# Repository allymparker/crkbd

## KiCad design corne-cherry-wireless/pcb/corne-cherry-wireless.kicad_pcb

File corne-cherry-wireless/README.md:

# Corne Choc Wireless

## Motivation
- Love the Corne form factor
- Love Nice!Nano
- Want Nice!View with no monkey patching
- Love the Ultralight, but want Choc Hotswap
  - Want the On/Off switch
  - Want the JST connector

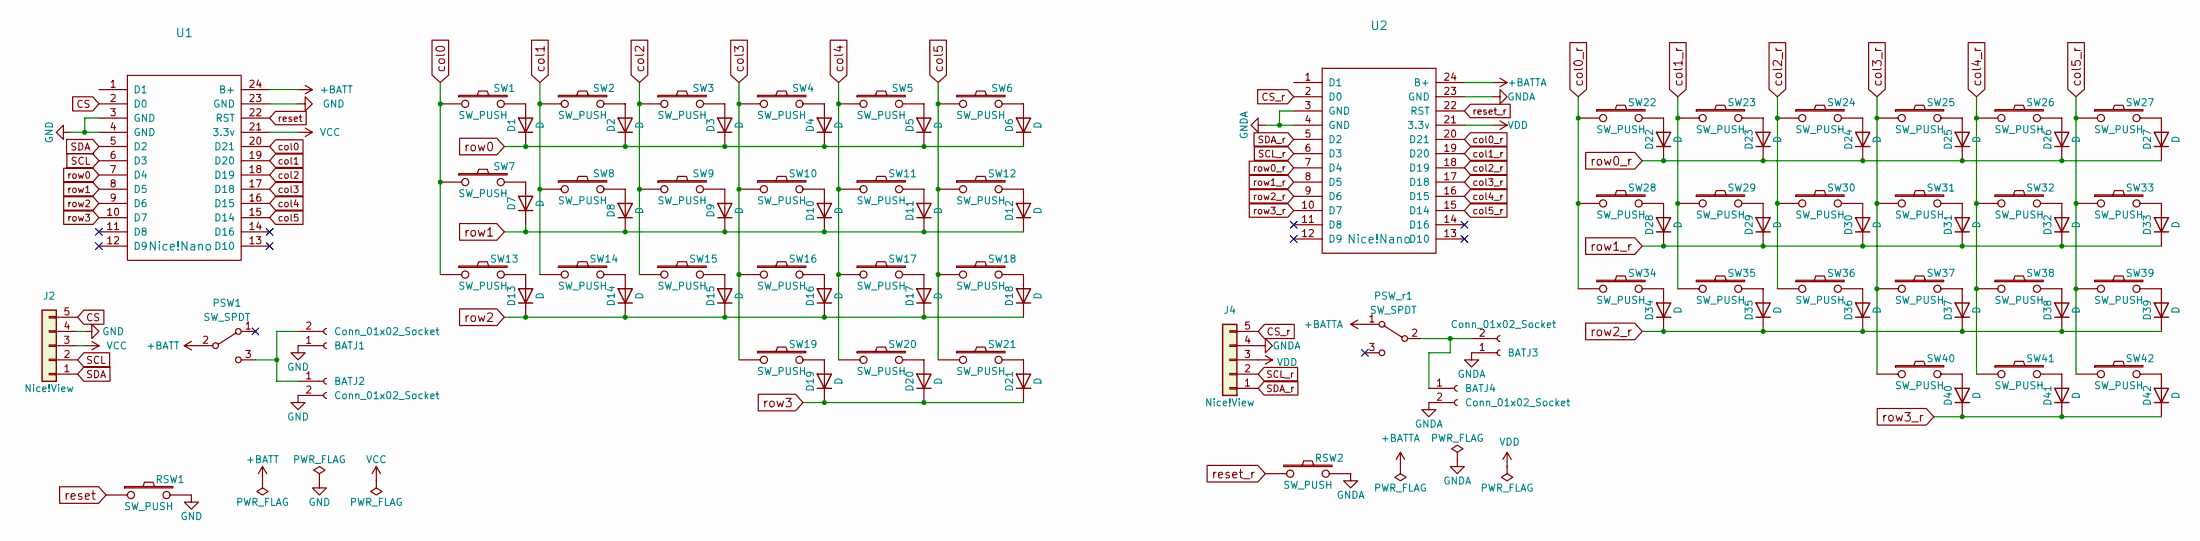
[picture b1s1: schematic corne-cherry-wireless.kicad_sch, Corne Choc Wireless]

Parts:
BATJ1, BATJ3: Conn_01x02_Socket; PinHeader_1x02_P2.54mm_Vertical
BATJ2, BATJ4: Conn_01x02_Socket; JST_PH_S2B-PH-K_1x02_P2.00mm_Horizontal
D1, D2, D3, D4, D5, D6, D7, D8, D9, D10, D11, D12, D13, D14, D15, D16, D17, D18, D19, D20, D21, D22, D23, D24, D25, D26, D27, D28, D29, D30, D31, D32, D33, D34, D35, D36, D37, D38, D39, D40, D41, D42: D; D3_SMD_v2
J2, J4: Nice!View; nice_view_1side
PSW1: SW_SPDT; SW_SPDT_PCM12
PSW_r1: SW_SPDT; SW_SPDT_PCM12
RSW1, RSW2: SW_PUSH; ResetSW_1side
SW1, SW2, SW3, SW4, SW5, SW6, SW7, SW8, SW9, SW10, SW11, SW12, SW13, SW14, SW15, SW16, SW17, SW18, SW19, SW20, SW22, SW23, SW24, SW25, SW26, SW27, SW28, SW29, SW30, SW31, SW32, SW33, SW34, SW35, SW36, SW37, SW38, SW39, SW40, SW41: SW_PUSH; CherryMX_Hotswap
SW21, SW42: SW_PUSH; CherryMX_Hotswap_1.5u
U1, U2: Nice!Nano; ProMicro_v3

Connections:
+BATT: PSW1.2 (B), U1.24 (B+)
+BATTA: PSW_r1.1 (A), U2.24 (B+)
CS: J2.5, U1.2 (D0)
CS_r: J4.5, U2.2 (D0)
GND: BATJ1.1, BATJ2.2, J2.4, RSW1.2, U1.3 (GND), U1.4 (GND), U1.23 (GND)
GNDA: BATJ3.1, BATJ4.2, J4.4, RSW2.2, U2.3 (GND), U2.4 (GND), U2.23 (GND)
unnamed: BATJ1.2, BATJ2.1, PSW1.3 (C)
unnamed: BATJ3.2, BATJ4.1, PSW_r1.2 (B)
unnamed: D1.2 (A), SW1.2
unnamed: D2.2 (A), SW2.2
unnamed: D3.2 (A), SW3.2
unnamed: D4.2 (A), SW4.2
unnamed: D5.2 (A), SW5.2
unnamed: D6.2 (A), SW6.2
unnamed: D7.2 (A), SW7.2
unnamed: D8.2 (A), SW8.2
unnamed: D9.2 (A), SW9.2
unnamed: D10.2 (A), SW10.2
unnamed: D11.2 (A), SW11.2
unnamed: D12.2 (A), SW12.2
unnamed: D13.2 (A), SW13.2
unnamed: D14.2 (A), SW14.2
unnamed: D15.2 (A), SW15.2
unnamed: D16.2 (A), SW16.2
unnamed: D17.2 (A), SW17.2
unnamed: D18.2 (A), SW18.2
unnamed: D19.2 (A), SW19.2
unnamed: D20.2 (A), SW20.2
unnamed: D21.2 (A), SW21.2
unnamed: D22.2 (A), SW22.2
unnamed: D23.2 (A), SW23.2
unnamed: D24.2 (A), SW24.2
unnamed: D25.2 (A), SW25.2
unnamed: D26.2 (A), SW26.2
unnamed: D27.2 (A), SW27.2
unnamed: D28.2 (A), SW28.2
unnamed: D29.2 (A), SW29.2
unnamed: D30.2 (A), SW30.2
unnamed: D31.2 (A), SW31.2
unnamed: D32.2 (A), SW32.2
unnamed: D33.2 (A), SW33.2
unnamed: D34.2 (A), SW34.2
unnamed: D35.2 (A), SW35.2
unnamed: D36.2 (A), SW36.2
unnamed: D37.2 (A), SW37.2
unnamed: D38.2 (A), SW38.2
unnamed: D39.2 (A), SW39.2
unnamed: D40.2 (A), SW40.2
unnamed: D41.2 (A), SW41.2
unnamed: D42.2 (A), SW42.2
SCL: J2.2, U1.6 (D3)
SCL_r: J4.2, U2.6 (D3)
SDA: J2.1, U1.5 (D2)
SDA_r: J4.1, U2.5 (D2)
VCC: J2.3, U1.21 (3.3v)
VDD: J4.3, U2.21 (3.3v)
col0: SW1.1, SW7.1, SW13.1, U1.20 (D21)
col0_r: SW22.1, SW28.1, SW34.1, U2.20 (D21)
col1: SW2.1, SW8.1, SW14.1, U1.19 (D20)
col1_r: SW23.1, SW29.1, SW35.1, U2.19 (D20)
col2: SW3.1, SW9.1, SW15.1, U1.18 (D19)
col2_r: SW24.1, SW30.1, SW36.1, U2.18 (D19)
col3: SW4.1, SW10.1, SW16.1, SW19.1, U1.17 (D18)
col3_r: SW25.1, SW31.1, SW37.1, SW40.1, U2.17 (D18)
col4: SW5.1, SW11.1, SW17.1, SW20.1, U1.16 (D15)
col4_r: SW26.1, SW32.1, SW38.1, SW41.1, U2.16 (D15)
col5: SW6.1, SW12.1, SW18.1, SW21.1, U1.15 (D14)
col5_r: SW27.1, SW33.1, SW39.1, SW42.1, U2.15 (D14)
reset: RSW1.1, U1.22 (RST)
reset_r: RSW2.1, U2.22 (RST)
row0: D1.1 (K), D2.1 (K), D3.1 (K), D4.1 (K), D5.1 (K), D6.1 (K), U1.7 (D4)
row0_r: D22.1 (K), D23.1 (K), D24.1 (K), D25.1 (K), D26.1 (K), D27.1 (K), U2.7 (D4)
row1: D7.1 (K), D8.1 (K), D9.1 (K), D10.1 (K), D11.1 (K), D12.1 (K), U1.8 (D5)
row1_r: D28.1 (K), D29.1 (K), D30.1 (K), D31.1 (K), D32.1 (K), D33.1 (K), U2.8 (D5)
row2: D13.1 (K), D14.1 (K), D15.1 (K), D16.1 (K), D17.1 (K), D18.1 (K), U1.9 (D6)
row2_r: D34.1 (K), D35.1 (K), D36.1 (K), D37.1 (K), D38.1 (K), D39.1 (K), U2.9 (D6)
row3: D19.1 (K), D20.1 (K), D21.1 (K), U1.10 (D7)
row3_r: D40.1 (K), D41.1 (K), D42.1 (K), U2.10 (D7)

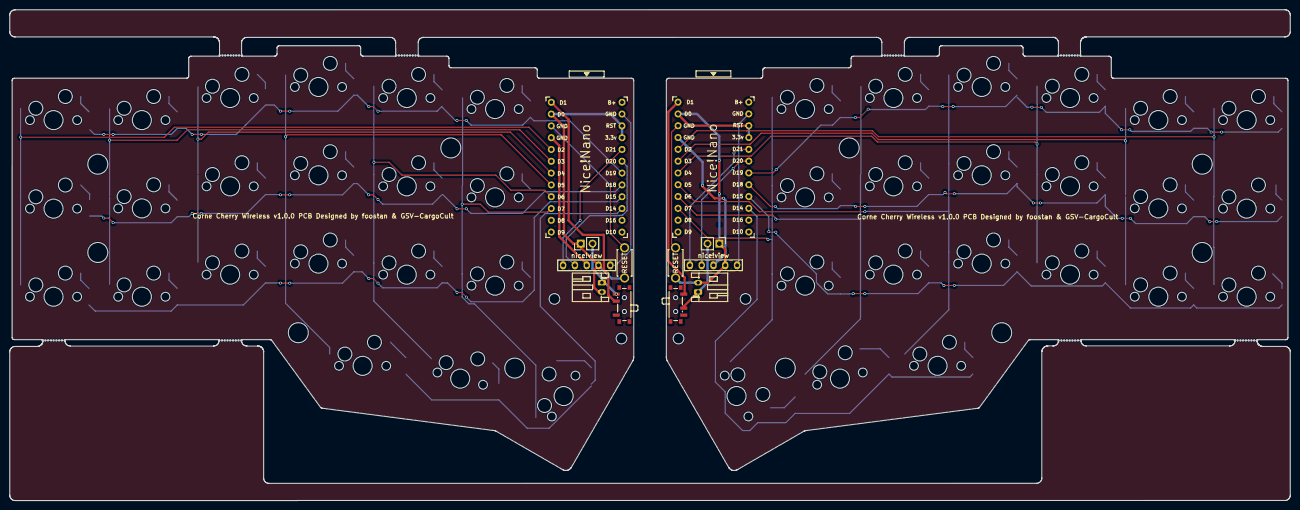
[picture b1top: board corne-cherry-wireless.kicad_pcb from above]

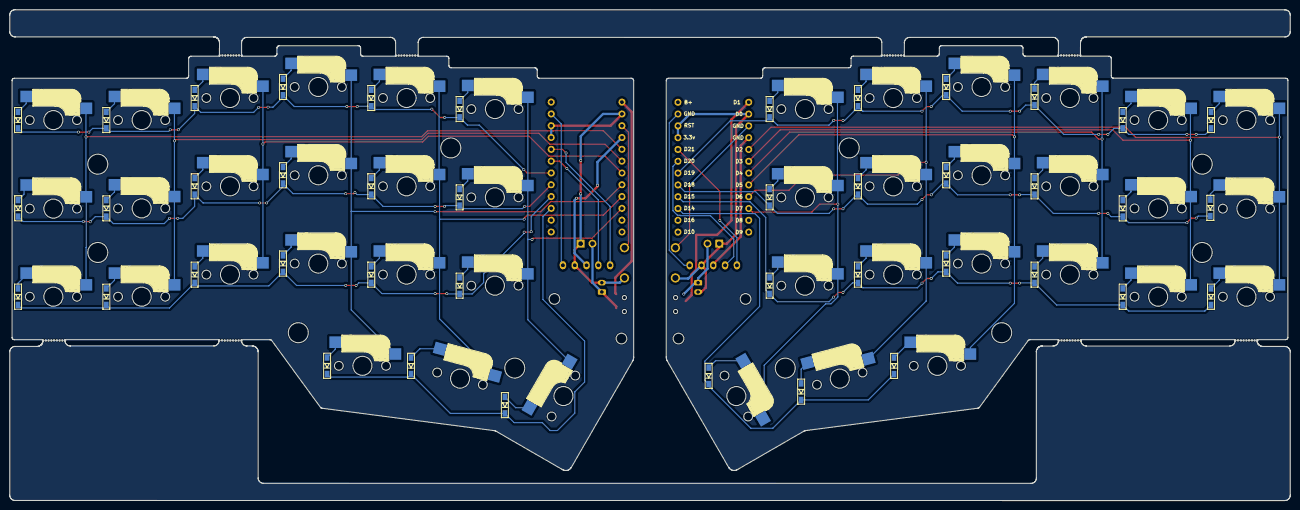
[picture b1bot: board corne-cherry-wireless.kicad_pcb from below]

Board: 2 copper layers, 275.5 x 105.6 mm, 97 parts (43 on the bottom side), 78 nets.

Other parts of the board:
locked: locked; Breakaway_Tabs

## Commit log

2023-10-09 Copy cherry and add submodules
2023-10-09 Add encoder switches
2023-10-09 ignore kicad
2023-10-09 Change to 5 pin for N!V
2023-10-09 Wire up encoder
2023-10-09 Rename and wire up Nice!Views
2023-10-09 Add Readme
2023-10-09 +BATTA
2023-10-10 Map new footprints
2023-10-10 Ignore temp files
2023-10-13 move things to the right place
2023-10-13 Readd screw holes
2023-10-13 Fix edge cuts
2023-10-13 Fix holes
2023-10-27 All traces done
2023-10-27 Tweak tracks
2023-10-27 Wide tracks
2023-10-27 Tweak roller pos
2023-10-27 Filled zones
2023-10-27 Rotate right encoder
2023-11-07 Choc Done YAY
2023-11-07 Add lib
2023-11-07 Ignore Production
2023-11-07 Silkscreen
2023-11-07 Add Cherry wireless submodules
2023-11-07 Rename files
2023-11-07 Replace rollers with switches
2023-11-07 Replace promicro with nn
2023-11-07 Add Cherry wireless
2023-11-07 Add submodules
2023-11-09 Missing holes
2024-01-05 corne LP plate
2024-01-12 Corneroll plates
2024-01-12 Fix DRC errors :(
2024-02-16 Shift NiceView and bat up so JST isn't obstructed by standoffs
2024-02-16 Fix labelling
2024-05-30 Rename
2024-05-30 Rename to corneroll
2024-05-31 Add more notes
